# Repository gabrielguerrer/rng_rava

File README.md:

# RAVA: an Open Hardware True Random Number Generator based on Avalanche Noise

RAVA is an open-source True Random Number Generator (TRNG) designed to offer a transparent and customizable platform, making auditalbe and high-quality entropy accessible to a wider audience. 
The RAVA device's main characteristics are:

- High-quality entropy: Producing unbiased and independent random bits without a post-processing algorithm.

- Differential design: Aiming towards immunity to environmental conditions by comparing two similar and independent noise sources.

- Dual entropy core: Incorporating two parallel and independent entropy channels that simultaneously produce random bytes. The dual design provides redundancy, a double output rate, or a unique feature for experiments employing a condition/control design.

- Full transparency: As an open-source project providing complete access to the circuit design, firmware, and user-side software, including drivers, libraries, and utilities.  At the hardware level, monitoring headers allow real-time inspection of voltages and noise sources during operation.

- Customizability: Offering interface headers for integration with other circuits, sensors, and integrated circuit (IC) components. Users have full control over the device's operation by sending commands through a communication interface. Moreover, as an open-source project, the firmware can be updated to modify the circuit's behavior and implement new functionalities.

- Accessibility: As a discrete circuit employing low-cost IC components and SMD resistors and capacitors of size 0805. Ensuring that the device remains affordable and can be assembled by users through manual soldering of the components to the printed circuit board. 

## Publication

For a comprehensive overview, encompassing an in-depth exploration of the noise source, a stochastic model, and statistical tests, please consult the article
- [IEEE Access, DOI: 10.1109/ACCESS.2023.3327325](https://ieeexplore.ieee.org/document/10295491)

## Schematics

The v1.0 implementation is presented as a discrete circuit with an ATmega32U4 microcontroller and a USB interface, achieving an unbiased throughput of 136.0 Kbits/s.

## Entropy

The physical phenomenon associated with the RAVA circuit’s entropy is the avalanche breakdown of reverse-biased diodes and the time unpredictability of those events.

A 25.5V voltage is applied to two reverse-biased 24V Zener diodes, inducing avalanche breakdown.
Next, the noise voltages are buffered using operational amplifiers (OA1, OA3). The purpose of the buffering stage is to prevent distortions that could be introduced in the subsequent steps.
The noise voltages are then DC decoupled and raised to a common level of 2.5V using unity-gain operational amplifiers (OA2, OA4). 
These operations result in the *avalanche noise* channels V_A1 and V_A2 containing the original noise voltages, which have been inverted and raised to the 2.5V DC level.

Finally, the analog channels V_A1 and V_A2 are connected to a comparator IC, which produces a digital output V_CMP representing which Zener produces the largest avalanche noise at a given time.
The V_CMP output, referred to as *differential noise*, consists of a sequence of pulses with varying lengths and unknown rising edge times. 
The interval between successive pulses depends on the avalanche breakdown occurring in the reverse-biased Zener diodes. 
Consequently, the pulses' intervals are inherently unpredictable, serving as an entropy source for the circuit.

Below is an example showcasing data for V_A1, V_A2, and V_CMP

The noise source output V_CMP is wired to a timer/counter port in the microcontroller configured to count the measured rising edge pulses.
Every ith-random bit is generated by evaluating the *pulse count* after a fixed *sampling interval*. 
The i-th bit results in 0 if the pulse count is even and 1 if odd.
The example reveals nine pulses in the sampling interval of 3 mus that would result in a 1 bit.

## Documentation

- [RAVA ‐ Assembling and Inspecting](https://github.com/gabrielguerrer/rng_rava/wiki/RAVA-Device-%E2%80%90-Assembling-and-Inspecting)
- [RAVA Firmware ‐ Installation](https://github.com/gabrielguerrer/rng_rava_firmware/wiki/RAVA-Firmware-%E2%80%90-Installation)
- [RAVA Firmware ‐ How it works](https://github.com/gabrielguerrer/rng_rava_firmware/wiki/RAVA-Firmware-%E2%80%90-How-it-works)
- [RAVA Python Driver - Installation and Usage](https://github.com/gabrielguerrer/rng_rava_driver_py)
- [RAVA Python Diagnostics - Statistical Tests](https://github.com/gabrielguerrer/rng_rava_diagnostics_py/wiki/Statistical-Tests)

## Associated projects

- [RAVA Firmware](https://github.com/gabrielguerrer/rng_rava_firmware)
- [RAVA Python Driver](https://github.com/gabrielguerrer/rng_rava_driver_py)
- [RAVA Python Diagnostics](https://github.com/gabrielguerrer/rng_rava_diagnostics_py)

## Contact

gabrielguerrer [at] gmail [dot] com

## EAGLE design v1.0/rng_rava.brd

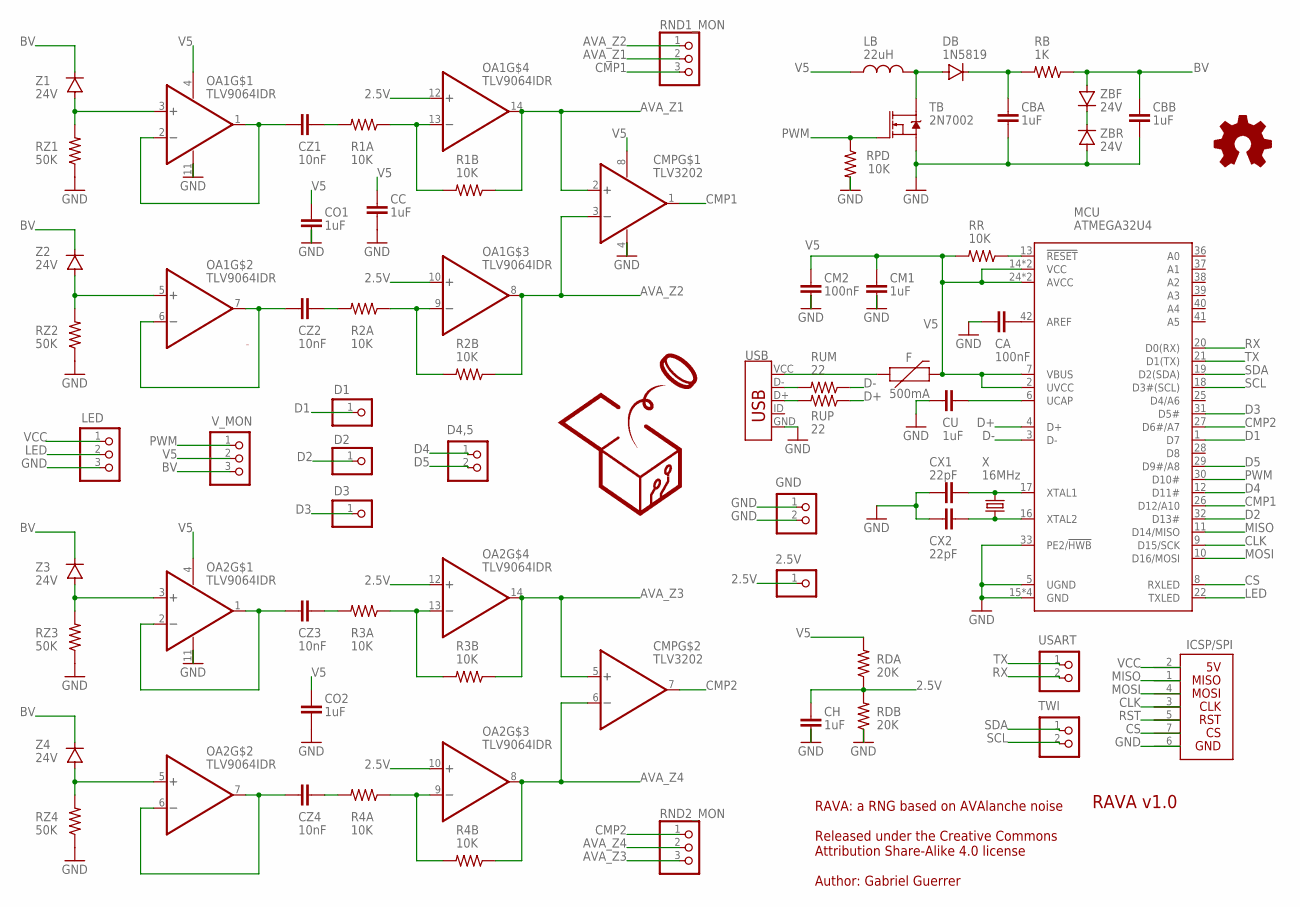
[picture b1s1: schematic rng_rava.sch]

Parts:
2.5V: PINHD-1X1LARGE; 1X01LARGE
CA: 100nF; 0805; LCSC_PART C28323
CBA: 1uF; 0805; LCSC_PART C28323
CBB: 1uF; 0805; LCSC_PART C28323
CC: 1uF; 0805; LCSC_PART C28323
CH: 1uF; 0805; LCSC_PART C28323
CM1: 1uF; 0805; LCSC_PART C28323
CM2: 100nF; 0805; LCSC_PART C28323
CMP: TLV3202; SOIC8; LCSC_PART C129325
CO1, CO2: 1uF; 0805; LCSC_PART C28323
CU: 1uF; 0805; LCSC_PART C28323
CX1, CX2: 22pF; 0805; LCSC_PART C1804
CZ1, CZ2, CZ3, CZ4: 10nF; 0805; LCSC_PART C1710
D1, D2, D3: PINHD-1X1LARGE; 1X01LARGE
D4,5: PINHD-1X2; 1X02
DB: 1N5819; SOD-323; LCSC_PART C369937
F: 500mA; 0805
GND: PINHD-1X2; 1X02
ICSP/SPI: ICSP-CS; 2X04
LB: 22uH; 0805; LCSC_PART C223170
LED: PINHD-1X3; 1X03
MCU: ATMEGA32U4; TQFP44; LCSC_PART C44854
OA1, OA2: TLV9064IDR; SOIC127P600X175-14N; LCSC_PART C388176
R1A, R1B, R2A, R2B, R3A, R3B, R4A, R4B: 10K; 0805; LCSC_PART C276215
RB: 1K; 0805; LCSC_PART C317261
RDA: 20K; 0805; LCSC_PART C4328
RDB: 20K; 0805; LCSC_PART C4328
RND1_MON, RND2_MON: PINHD-1X3; 1X03
RPD: 10K; 0805; LCSC_PART C317261
RR: 10K; 0805; LCSC_PART C276215
RUM: 22; 0805; LCSC_PART C17561
RUP: 22; 0805; LCSC_PART C17561
RZ1, RZ2, RZ3, RZ4: 50K; 0805; LCSC_PART C276216
TB: 2N7002; SOT323; LCSC_PART C139444
TWI: PINHD-1X2; 1X02
USART: PINHD-1X2; 1X02
USB: C40957; U254-051N-4BH806; LCSC_PART C319170
V_MON: PINHD-1X3; 1X03
X: 16MHz; SMD_5032; LCSC_PART C115962
Z1, Z2, Z3, Z4: 24V; SOD-323; LCSC_PART C118615
ZBF: 24V; SOD-323; LCSC_PART C118615
ZBR: 24V; SOD-323; LCSC_PART C118615

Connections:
2.5V: 2.5V.1, CH.2, OA1.10 (+IN), OA1.12 (+IN), OA2.10 (+IN), OA2.12 (+IN), RDA.1, RDB.2
AVA_Z1: CMP.2 (+IN), OA1.14 (OUT), R1B.1, RND1_MON.2
AVA_Z2: CMP.3 (-IN), OA1.8 (OUT), R2B.1, RND1_MON.1
AVA_Z3: CMP.5 (+IN), OA2.14 (OUT), R3B.1, RND2_MON.3
AVA_Z4: CMP.6 (-IN), OA2.8 (OUT), R4B.1, RND2_MON.2
BV: CBB.1, RB.1, V_MON.3, Z1.C, Z2.C, Z3.C, Z4.C, ZBF.A
CLK: ICSP/SPI.3 (CLK), MCU.9 (D15/SCK)
CMP1: CMP.1 (OUT), MCU.26 (D12/A10), RND1_MON.3
CMP2: CMP.7 (OUT), MCU.27 (D6#/A7), RND2_MON.1
CS: ICSP/SPI.7 (CS), MCU.8 (RXLED)
D1: D1.1, MCU.1 (D7)
D2: D2.1, MCU.32 (D13#)
D3: D3.1, MCU.31 (D5#)
D4: D4,5.1, MCU.12 (D11#)
D5: D4,5.2, MCU.29 (D9#/A8)
D+: MCU.4 (D+), RUP.1
D-: MCU.3 (D-), RUM.1
GND: CA.1, CBA.2, CBB.2, CC.2, CH.1, CM1.1, CM2.1, CMP.4 (GND), CO1.2, CO2.2, CU.1, CX1.2, CX2.2, GND.1, GND.2, ICSP/SPI.6 (GND), LED.3, MCU.5 (UGND), MCU.15 (GND), MCU.23 (GND), MCU.33 (PE2/!HWB), MCU.35 (GND), MCU.43 (GND), OA1.11 (GND), OA2.11 (GND), RDB.1, RPD.2, RZ1.1, RZ2.1, RZ3.1, RZ4.1, TB.2 (S), USB.GND, ZBR.A
LED: LED.2, MCU.22 (TXLED)
MISO: ICSP/SPI.1 (MISO), MCU.11 (D14/MISO)
MOSI: ICSP/SPI.4 (MOSI), MCU.10 (D16/MOSI)
unnamed: CZ1.2, R1A.2
unnamed: CZ1.1, OA1.1 (OUT), OA1.2 (-IN)
unnamed: OA1.3 (+IN), RZ1.2, Z1.A
unnamed: OA1.13 (-IN), R1A.1, R1B.2
unnamed: CZ2.1, OA1.6 (-IN), OA1.7 (OUT)
unnamed: OA1.5 (+IN), RZ2.2, Z2.A
unnamed: CZ2.2, R2A.2
unnamed: OA1.9 (-IN), R2A.1, R2B.2
unnamed: CZ3.1, OA2.1 (OUT), OA2.2 (-IN)
unnamed: OA2.3 (+IN), RZ3.2, Z3.A
unnamed: CZ3.2, R3A.2
unnamed: OA2.13 (-IN), R3A.1, R3B.2
unnamed: CZ4.1, OA2.6 (-IN), OA2.7 (OUT)
unnamed: OA2.5 (+IN), RZ4.2, Z4.A
unnamed: CZ4.2, R4A.2
unnamed: OA2.9 (-IN), R4A.1, R4B.2
unnamed: DB.A, LB.2, TB.3 (D)
unnamed: CBA.1, DB.C, RB.2
unnamed: ZBF.C, ZBR.C
unnamed: CU.2, MCU.6 (UCAP)
unnamed: RUM.2, USB.D-
unnamed: RUP.2, USB.D+
unnamed: CX1.1, MCU.17 (XTAL1), X.P$2 (2)
unnamed: CX2.1, MCU.16 (XTAL2), X.P$1 (1)
unnamed: CA.2, MCU.42 (AREF)
PWM: MCU.30 (D10#), RPD.1, TB.1 (G), V_MON.1
RST: ICSP/SPI.5 (RST), MCU.13 (!RESET), RR.1
RX: MCU.20 (D0(RX)), USART.2
SCL: MCU.18 (D3#(SCL)), TWI.2
SDA: MCU.19 (D2(SDA)), TWI.1
TX: MCU.21 (D1(TX)), USART.1
V5: CC.1, CM1.2, CM2.2, CMP.8 (VCC), CO1.1, CO2.1, F.2, LB.1, MCU.2 (UVCC), MCU.7 (VBUS), MCU.14 (VCC), MCU.24 (AVCC), MCU.34 (VCC), MCU.44 (AVCC), OA1.4 (VCC), OA2.4 (VCC), RDA.2, RR.2, V_MON.2
VCC: F.1, ICSP/SPI.2 (VCC_3V), LED.1, USB.VCC (VBUS)

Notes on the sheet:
RAVA: a RNG based on AVAlanche noise Released under the Creative Commons Attribution Share-Alike 4.0 license Author: Gabriel Guerrer
RAVA v1.0

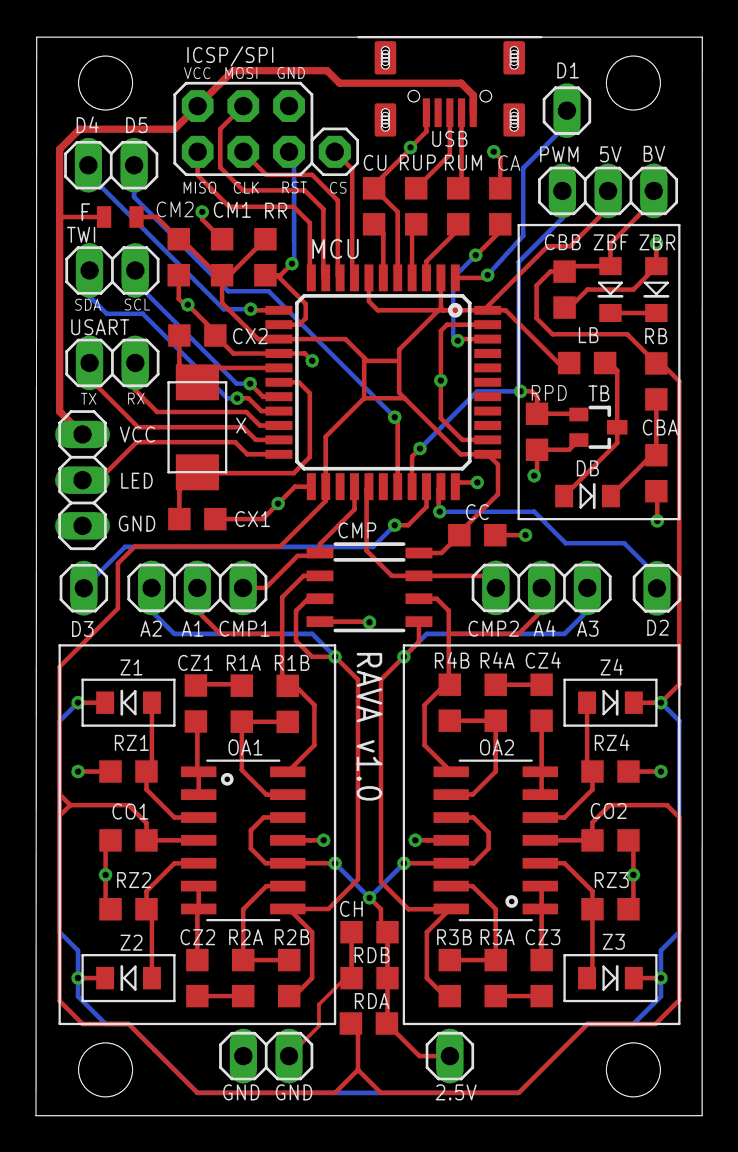
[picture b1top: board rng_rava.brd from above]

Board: 2 copper layers, 37.0 x 59.9 mm, 64 parts (0 on the bottom side), 54 nets.

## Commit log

2023-05-02 updating readme and licence
2023-05-02 updating licence
2023-05-02 updating folder structure
2023-05-02 license update
2023-05-03 uploading hardware v1.0
2023-05-03 updating
2023-05-31 readme updates
2023-05-31 testing logo
2023-05-31 testing logo2
2023-05-31 logo test
2023-05-31 testing logo final
2023-05-31 updating logo
2023-08-09 First upload
2023-08-09 fixing readme links
2023-08-11 wiki images
2023-08-11 wiki links
2023-08-12 bom v10 mfr part
2023-08-13 wiki imgs
2023-08-13 wiki img rename
2023-09-26 updating peripherals
2023-10-27 BOM: Including Quantity
2023-11-03 Publication update
2026-04-29 updating fuse image
2026-05-18 Updating fuses image

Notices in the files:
parts and their libraries:
SparkFun-IC-Microcontroller: Licensing: Creative Commons ShareAlike 4.0 International - https://creativecommons.org/licenses/by-sa/4.0
